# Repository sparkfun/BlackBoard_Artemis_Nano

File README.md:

**NOTE:** *This product has been retired from our catalog. There is an updated RedBoard version available: [DEV-15443](https://www.sparkfun.com/products/15443). If you are looking for more up-to-date info, please check out some of these resources to see how other users are still hacking and improving on this product version.*

* *[SparkFun Artemis Forum](https://forum.sparkfun.com/viewforum.php?f=167)*
* *[Comments Here on GitHub](https://github.com/sparkfun/BlackBoard_Artemis_Nano/issues)*

SparkFun BlackBoard Artemis Nano
============================

[  
*SparkFun BlackBoard Artemis Nano (SPX-15411)*](https://www.sparkfun.com/products/15411)

We like to joke the Artemis Nano is a party on the front and business on the back. And that's by design! All the important LEDs, connectors, labels, and buttons are presented on the front for the best user experience with all the supporting circuitry on the rear of the board. The BlackBoard Artemis Nano is a minimal but extremely handy implementation of the Artemis module. A light weight, 0.8mm thick PCB, with on board lipo-battery charging and a Qwiic connector, this board is easy to implement into very small projects. A dual row of ground connections make it easy to add lots of buttons, LEDs, and anything that requires its own GND connection. At the same time, the board is breadboard compatible! 

A modern USB-C connector makes programming easy. The Nano is fully compatible with the SparkFun's Arduino core and can be programmed easily under the Arduino IDE. We've also exposed the JTAG connector for more advanced users who prefer to use the power and speed of professional tools. If you're looking for a simple, cost-effective board to replace your aging Arduino Uno or Arduino Nano, look no further. We've even added a digital MEMS microphone for folks wanting to experiment with always-on voice commands with TensorFlow and machine learning.
 
With 1M flash and 384k RAM you'll have plenty of room for your sketches. The Artemis module runs at 48MHz with a 96MHz turbo mode available and with Bluetooth to boot!

The SparkFun Artemis Nano is an incredibly flexible device for a small footprint but if you're looking for all the bells and whistles, be sure to checkout our BlackBoard and ATP footprints for even more I/O and capabilities.

Repository Contents
-------------------
* **/Hardware** - Eagle design files (.brd, .sch)

Documentation
-------------------

* **[Hookup Guide for the BlackBoard Artemis Nano](https://learn.sparkfun.com/tutorials/hookup-guide-for-the-blackboard-artemis-nano)**
* **[Designing with the SparkFun Artemis](https://learn.sparkfun.com/tutorials/designing-with-the-sparkfun-artemis)** - Layout and design considerations when using the Artemis module.
* **[Artemis Development with Arduino](https://learn.sparkfun.com/tutorials/artemis-development-with-arduino)** - Introduction to the Arduino core for the Artemis Module.
* **[Ambiq Apollo3 SDK SetUp](https://learn.sparkfun.com/tutorials/using-sparkfun-edge-board-with-ambiq-apollo3-sdk)** - Getting set up with the Apollo3 Software Development Kit.
* **[CH340E USB to serial IC Drivers](https://www.sparkfun.com/ch340)**
* **[SparkFun Fritzing repo](https://github.com/sparkfun/Fritzing_Parts)** - Fritzing diagrams for SparkFun products.

License Information
-------------------

This product is _**open source**_! 

Please review the LICENSE.md file for license information. 

If you have any questions or concerns on licensing, please contact techsupport@sparkfun.com.

Please use, reuse, and modify these files as you see fit. Please maintain attribution to SparkFun Electronics and release any derivative under the same license.

Distributed as-is; no warranty is given.

- Your friends at SparkFun.

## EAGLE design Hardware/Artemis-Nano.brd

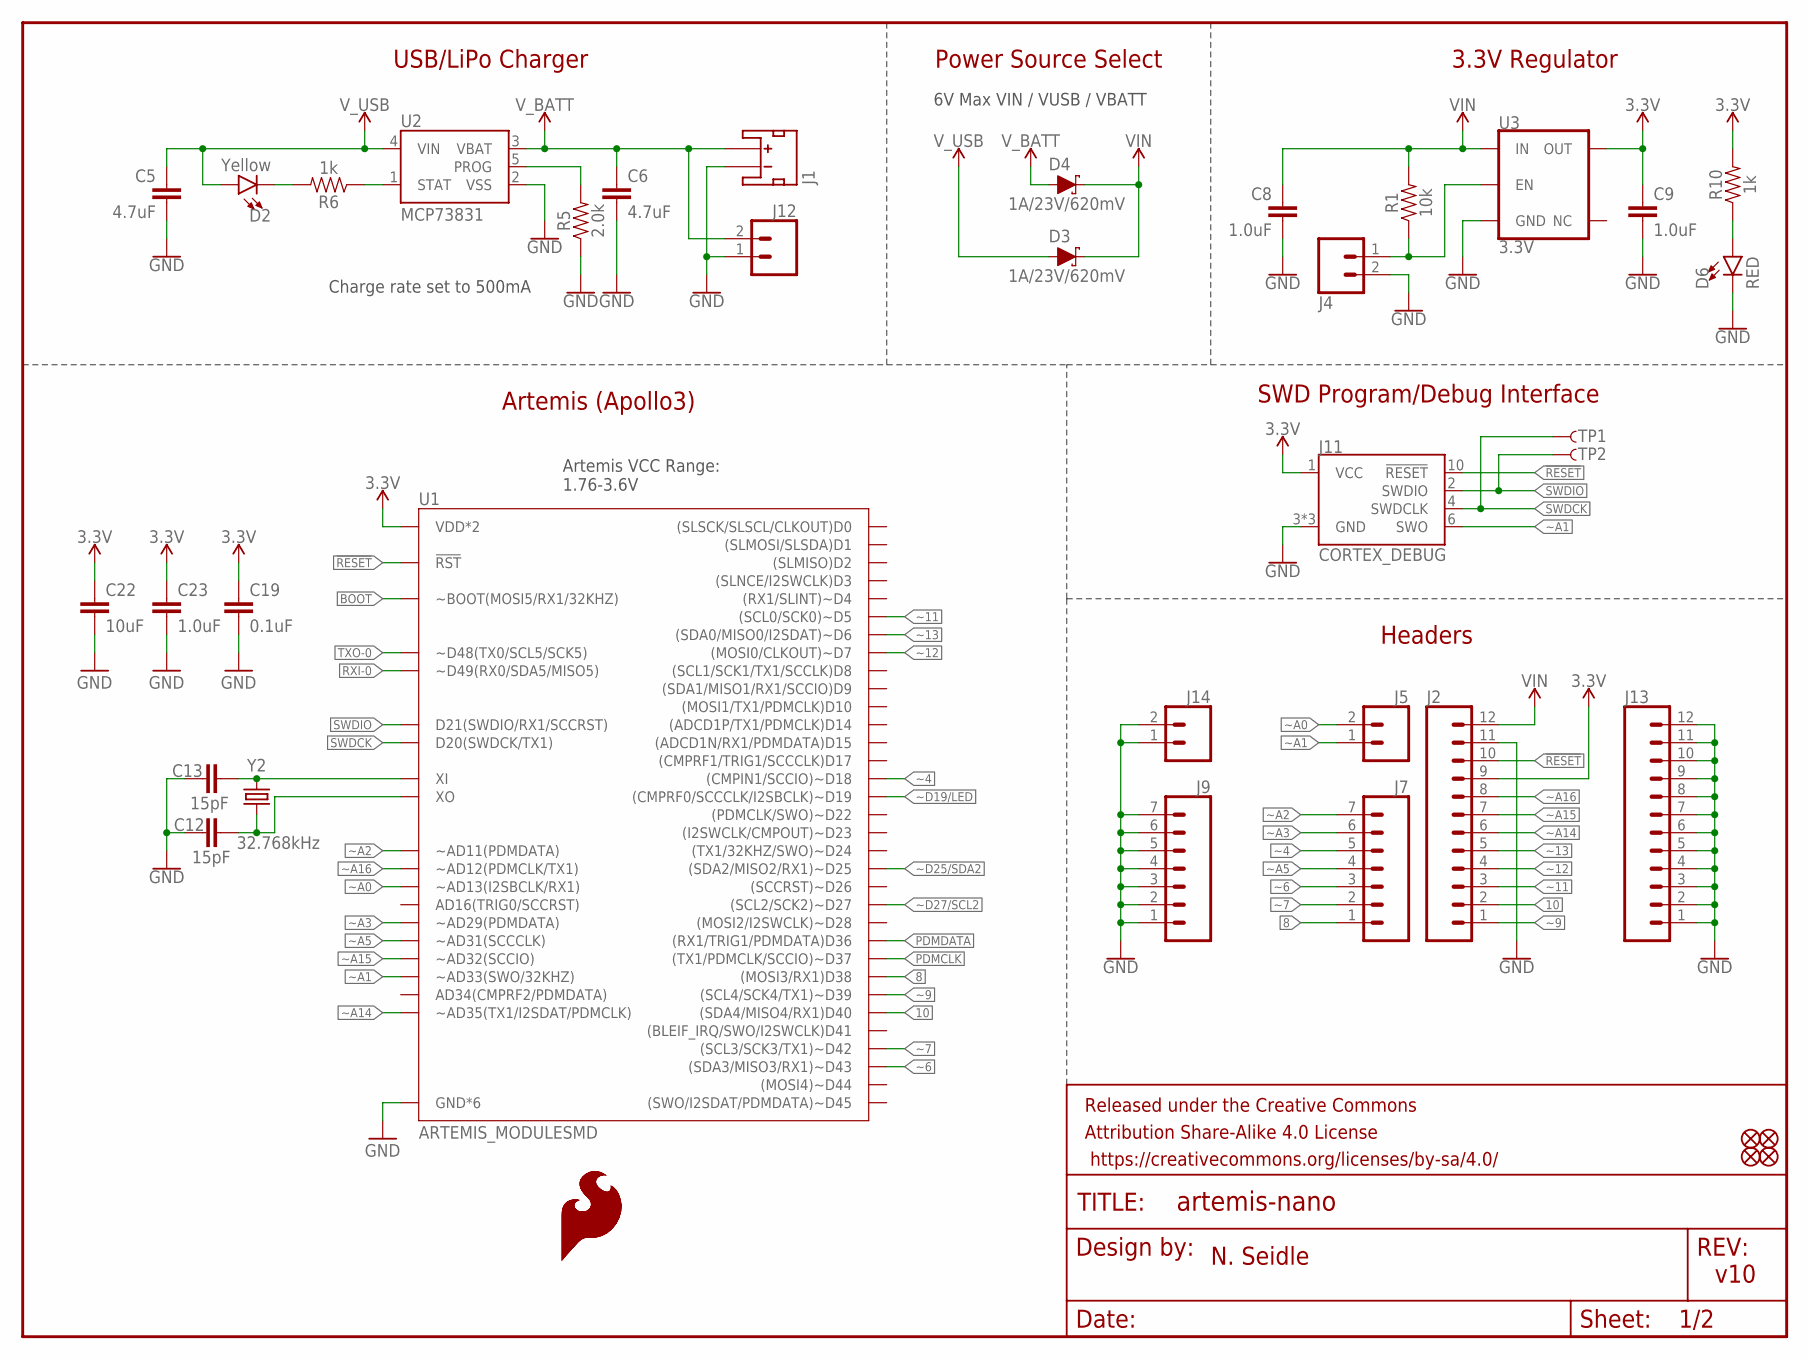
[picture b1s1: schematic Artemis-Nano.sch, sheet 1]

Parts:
C5, C6: 4.7uF; 0603
C8, C9, C23: 1.0uF; 0402-TIGHT
C12, C13: 15pF; 0603
C19: 0.1uF; 0402-TIGHT
C22: 10uF; 0603
D2: Yellow; LED-0603
D3, D4: 1A/23V/620mV; SOD-323
D6: RED; LED-0603
FD1, FD2, FD3, FD4: FIDUCIALUFIDUCIAL; FIDUCIAL-MICRO
FRAME1: FRAME-LETTER; CREATIVE_COMMONS
J1: JST_2MM_MALE; JST-2-SMD
J2, J13: CONN_12NO_SILK; 1X12_NO_SILK
J4, J5, J12, J14: CONN_021X02_NO_SILK; 1X02_NO_SILK
J7, J9: CONN_07NO_SILK; 1X07_NO_SILK
J11: CORTEX_DEBUG; 2X5-PTH-1.27MM-NO_SILK
LOGO1, LOGO4: SFE_LOGO_FLAME.1_INCH; SFE_LOGO_FLAME_.1
R1: 10k; 0603
R5: 2.0k; 0603
R6, R10: 1k; 0603
TP1, TP2: TEST-POINT3X5; PAD.03X.05
U1: ARTEMIS_MODULESMD; ARTEMIS_FP
U2: MCP73831; SOT23-5
U3: 3.3V; SOT23-5
Y2: 32.768kHz; CRYSTAL-SMD-3.2X1.5MM

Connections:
3.3V: C9.1, C19.2, C22.1, C23.1, J2.9, J11.1 (VCC), R10.2, U1.VDD@36 (VDD*2), U1.VDD@37 (VDD*2), U3.5 (OUT); also elsewhere on the board
8: J7.1, U1.D38 ((MOSI3/RX1)D38)
10: J2.2, U1.D40 ((SDA4/MISO4/RX1)D40)
!RESET: J2.10, J11.10 (!RESET), U1.~RST (!RST); also elsewhere on the board
BOOT: U1.BOOT (~BOOT(MOSI5/RX1/32KHZ)); also elsewhere on the board
GND: C5.2, C6.2, C8.2, C9.2, C12.1, C13.1, C19.1, C22.2, C23.2, D6.C, J1.1 (-), J2.11, J4.2, J9.1, J9.2, J9.3, J9.4, J9.5, J9.6, J9.7, J11.3 (GND), J11.5 (GND), J11.9 (GND), J12.1, J13.1, J13.2, J13.3, J13.4, J13.5, J13.6, J13.7, J13.8, J13.9, J13.10, J13.11, J13.12, J14.1, J14.2, R5.1, U1.GND@1 (GND*6), U1.GND@22 (GND*6), U1.GND@38 (GND*6), U1.GND@39 (GND*6), U1.GND@47 (GND*6), U1.GND@59 (GND*6), U2.2 (VSS), U3.2 (GND); also elsewhere on the board
unnamed: R5.2, U2.5 (PROG)
unnamed: C12.2, U1.XO, Y2.P$2 (2)
unnamed: D2.C, R6.2
unnamed: R6.1, U2.1 (STAT)
unnamed: C13.2, U1.XI, Y2.P$1 (1)
unnamed: D6.A, R10.1
PDMCLK: U1.~D37 ((TX1/PDMCLK/SCCIO)~D37); also elsewhere on the board
PDMDATA: U1.D36 ((RX1/TRIG1/PDMDATA)D36); also elsewhere on the board
RXI-0: U1.RXI-0 (~D49(RX0/SDA5/MISO5)); also elsewhere on the board
SWDCK: J11.4 (SWDCLK), TP1.P$1, U1.SWDCK (D20(SWDCK/TX1))
SWDIO: J11.2 (SWDIO), TP2.P$1, U1.SWDIO (D21(SWDIO/RX1/SCCRST))
TXO-0: U1.TXO-0 (~D48(TX0/SCL5/SCK5)); also elsewhere on the board
VIN: C8.1, D3.C, D4.C, J2.12, R1.2, U3.1 (IN)
VREG_EN: J4.1, R1.1, U3.3 (EN)
V_BATT: C6.1, D4.A, J1.2 (+), J12.2, U2.3 (VBAT)
V_USB: C5.1, D2.A, D3.A, U2.4 (VIN); also elsewhere on the board
~4: J7.5, U1.~D18 ((CMPIN1/SCCIO)~D18)
~6: J7.3, U1.~D43 ((SDA3/MISO3/RX1)~D43)
~7: J7.2, U1.~D42 ((SCL3/SCK3/TX1)~D42)
~9: J2.1, U1.~D39 ((SCL4/SCK4/TX1)~D39)
~11: J2.3, U1.~D5 ((SCL0/SCK0)~D5)
~12: J2.4, U1.D7 ((MOSI0/CLKOUT)~D7)
~13: J2.5, U1.~D6 ((SDA0/MISO0/I2SDAT)~D6)
~A0: J5.2, U1.~AD13 (~AD13(I2SBCLK/RX1))
~A1: J5.1, J11.6 (SWO), U1.~AD33/SWO (~AD33(SWO/32KHZ))
~A2: J7.7, U1.~AD11 (~AD11(PDMDATA))
~A3: J7.6, U1.~AD29 (~AD29(PDMDATA))
~A5: J7.4, U1.~AD31 (~AD31(SCCCLK))
~A14: J2.6, U1.~AD35 (~AD35(TX1/I2SDAT/PDMCLK))
~A15: J2.7, U1.~AD32 (~AD32(SCCIO))
~A16: J2.8, U1.~AD12 (~AD12(PDMCLK/TX1))
~D19/LED: U1.~D19 ((CMPRF0/SCCCLK/I2SBCLK)~D19); also elsewhere on the board
~D25/SDA2: U1.~D25 ((SDA2/MISO2/RX1)~D25); also elsewhere on the board
~D27/SCL2: U1.~D27 ((SCL2/SCK2)~D27); also elsewhere on the board

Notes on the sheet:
v10
N. Seidle
SWD Program/Debug Interface
Headers
Artemis (Apollo3)
USB/LiPo Charger
Power Source Select
3.3V Regulator
Artemis VCC Range: 1.76-3.6V
Charge rate set to 500mA
6V Max VIN / VUSB / VBATT

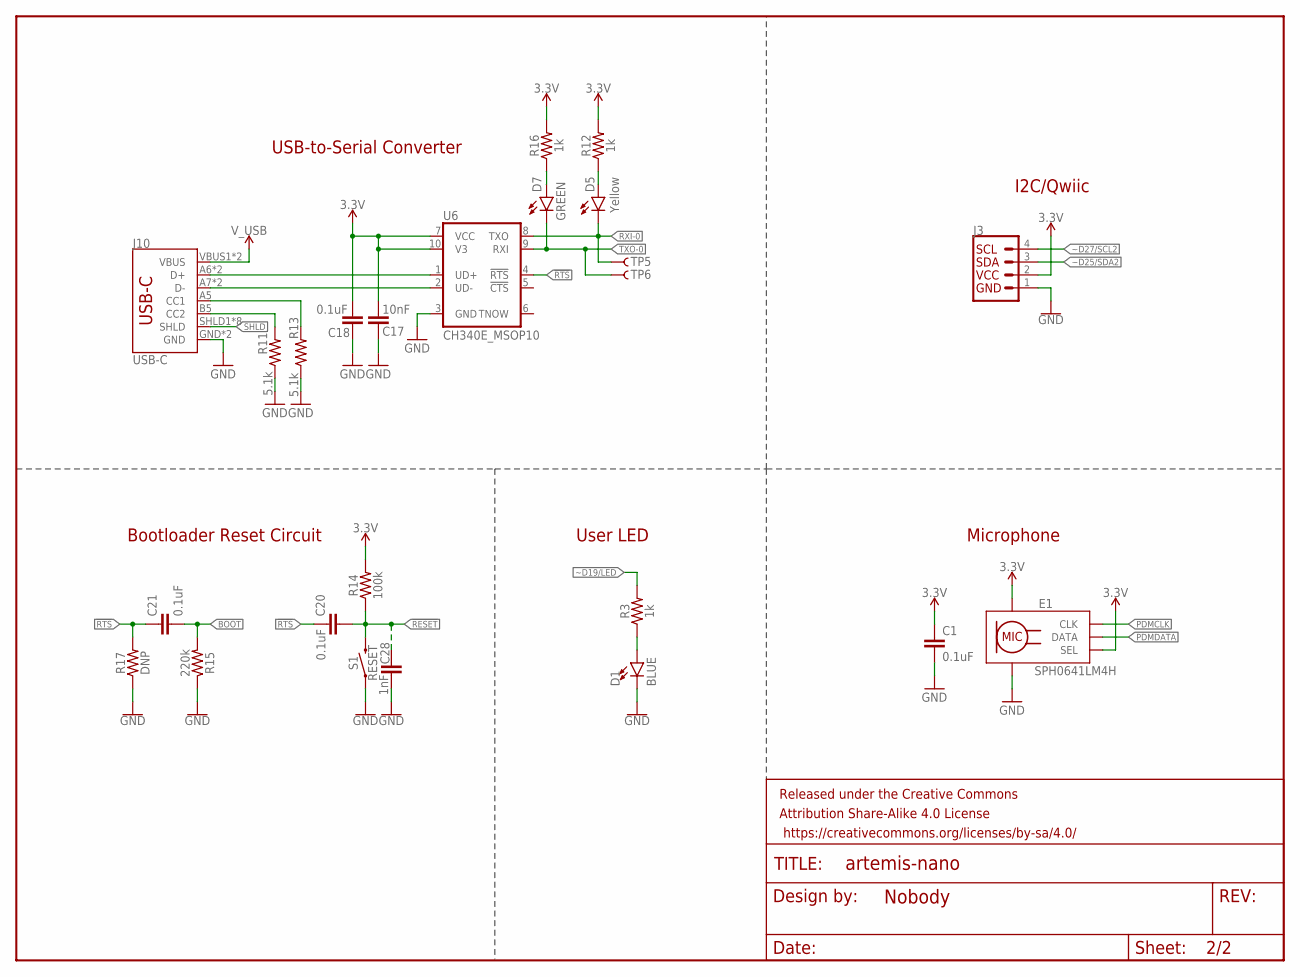
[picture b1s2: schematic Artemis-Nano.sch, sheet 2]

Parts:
C1: 0.1uF; 0402-TIGHT
C17: 10nF; 0603
C18, C20, C21: 0.1uF; 0603
C28: 1nF; 0603
D1: BLUE; LED-0603
D5: Yellow; LED-0603
D7: GREEN; LED-0603
E1: SPH0641LM4H; SPH0641LM4H-1_MICROPHONE
FRAME2: FRAME-LETTERNO_PACKAGE; DUMMY
J3: QWIIC_CONNECTORJS-1MM; JST04_1MM_RA
J10: USB-C; USB-C-16P
R3, R12, R16: 1k; 0603
R11, R13: 5.1k; 0603
R14: 100k; 0603
R15: 220k; 0603
R17: DNP; 0603
S1: RESET; TACTILE_SWITCH_SMD_4.6X2.8MM
TP5, TP6: TEST-POINT3X5; PAD.03X.05
U6: CH340E_MSOP10; MSOP10

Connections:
3.3V: C1.1, C17.1, C18.1, E1.2 (SEL), E1.5 (VDD), J3.2, R12.2, R14.2, R16.2, U6.7 (VCC), U6.10 (V3); also elsewhere on the board
!RESET: C20.2, C28.1, R14.1, S1.3 (2), S1.4 (2); also elsewhere on the board
!RTS: C20.1, C21.1, R17.2, U6.4 (!RTS)
BOOT: C21.2, R15.2; also elsewhere on the board
CC1: J10.A5 (CC1), R13.2
CC2: J10.B5 (CC2), R11.2
D+1: J10.A6 (D+), J10.B6 (D+), U6.1 (UD+)
D-1: J10.A7 (D-), J10.B7 (D-), U6.2 (UD-)
GND: C1.2, C17.2, C18.2, C28.2, D1.C, E1.3 (GND), E1.6 (GND), E1.7 (GND), E1.8 (GND), J3.1, J10.GND, J10.GND2 (GND), R11.1, R13.1, R15.1, R17.1, S1.1, S1.2 (1), U6.3 (GND); also elsewhere on the board
unnamed: D7.A, R16.1
unnamed: D1.A, R3.1
unnamed: D5.A, R12.1
PDMCLK: E1.4 (CLK); also elsewhere on the board
PDMDATA: E1.1 (DATA); also elsewhere on the board
RXI-0: D5.C, TP5.P$1, U6.8 (TXO); also elsewhere on the board
SHLD: J10.SHLD1 (SHLD), J10.SHLD2 (SHLD), J10.SHLD3 (SHLD), J10.SHLD4 (SHLD), J10.SHLD5 (SHLD), J10.SHLD6 (SHLD), J10.SHLD7 (SHLD), J10.SHLD8 (SHLD)
TXO-0: D7.C, TP6.P$1, U6.9 (RXI); also elsewhere on the board
V_USB: J10.VBUS1 (VBUS), J10.VBUS2 (VBUS); also elsewhere on the board
~D19/LED: R3.2; also elsewhere on the board
~D25/SDA2: J3.3; also elsewhere on the board
~D27/SCL2: J3.4; also elsewhere on the board

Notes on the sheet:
Microphone
USB-to-Serial Converter
Bootloader Reset Circuit
User LED
I2C/Qwiic

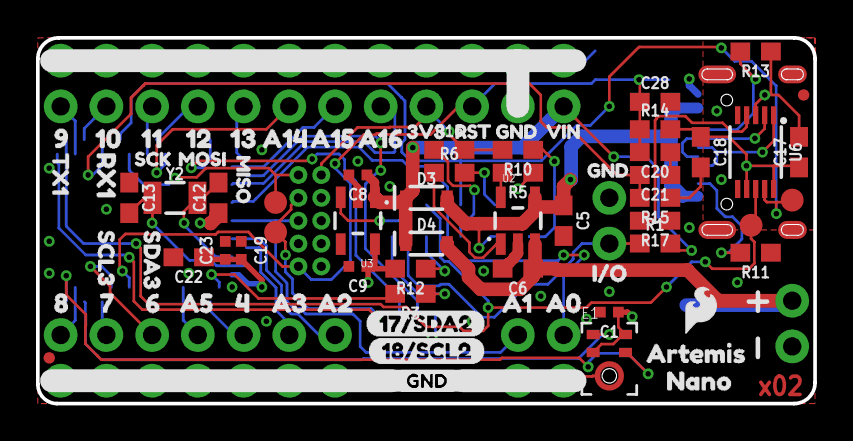
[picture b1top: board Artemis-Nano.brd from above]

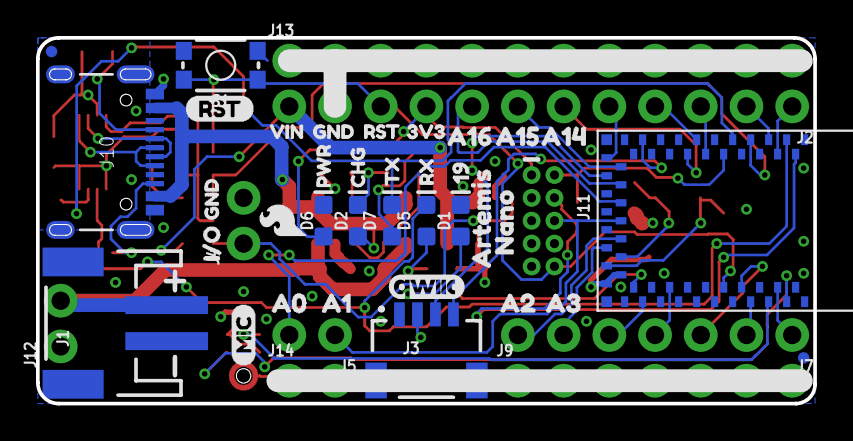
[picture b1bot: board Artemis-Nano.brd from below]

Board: 4 copper layers, 43.2 x 20.3 mm, 125 parts (47 on the bottom side), 49 nets.

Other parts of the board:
U$1, U$49: 3V316
U$2: ____GND____2
U$3, U$38: RST19
U$4, U$23: I#O3
U$5: CHG26
U$6: PWR27
U$7, U$29, U$33, U$43: GND17
U$8: QWIIC#LOGO#JPG
U$9, U$20: A00
U$10: A57
U$11: SCL30
U$12, U$54: A145
U$13, U$22: ARTEMIS6
U$14: MISO5
U$15: MIC0
U$16: MOSI4
U$17, U$24: NANO7
U$18: SCK3
U$19, U$42: A32
U$21, U$41: A21
U$25: PRODUCTION_INSTRUCTIONS
U$26: 191
U$27, U$39: VIN19
U$28, U$55: A156
U$30: GND2
U$31: SDA31
U$32: 46
U$34, U$40: A10
U$35: 68
U$36: 79
U$37: 810
U$45: 90
U$46: 101
U$47: 112
U$48, U$56: A167
U$50: RX10
U$51: RST1
U$52: 123
U$53: 134
U$57: 17#SDA21
U$59: TX12
U$60: 18#SCL20
U$85: RX23
U$86: TX22

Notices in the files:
parts and their libraries:
SparkFun-Aesthetics: Licensing: Creative Commons ShareAlike 4.0 International - https://creativecommons.org/licenses/by-sa/4.0
SparkFun-Aesthetics: Released under the Creative Commons Attribution Share-Alike 4.0 License
SparkFun-Aesthetics: https://creativecommons.org/licenses/by-sa/4.0
